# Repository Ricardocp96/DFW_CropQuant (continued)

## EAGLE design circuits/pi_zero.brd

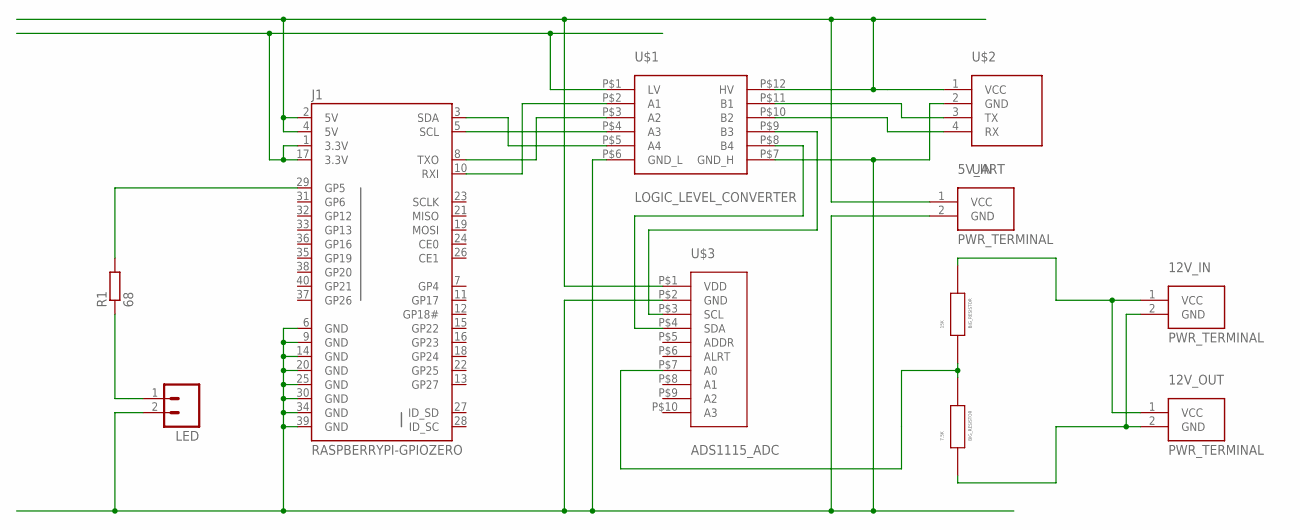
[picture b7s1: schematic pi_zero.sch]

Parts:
5V_IN, 12V_IN, 12V_OUT: PWR_TERMINAL
7.5K, 15K: BIG_RESISTOR
J1: RASPBERRYPI-GPIOZERO; 2X20-ZERO
LED: M02LOCK_LONGPADS; 1X02_LOCK_LONGPADS
R1: 68; 0204/7
U$1: LOGIC_LEVEL_CONVERTER
U$2: UART; I2C_TERM
U$3: ADS1115_ADC

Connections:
unnamed: J1.29 (GP5), R1.2
unnamed: LED.1, R1.1
unnamed: U$1.P$11 (B1), U$2.3 (TX)
unnamed: 5V_IN.1 (VCC), J1.2 (5V), J1.4 (5V), U$1.P$12 (HV), U$2.1 (VCC), U$3.P$1 (VDD)
unnamed: J1.1 (3.3V), J1.17 (3.3V), U$1.P$1 (LV)
unnamed: 5V_IN.2 (GND), J1.6 (GND), J1.9 (GND), J1.14 (GND), J1.20 (GND), J1.25 (GND), J1.30 (GND), J1.34 (GND), J1.39 (GND), LED.2, U$1.P$6 (GND_L), U$1.P$7 (GND_H), U$2.2 (GND), U$3.P$2 (GND)
unnamed: 7.5K.P$1, 12V_IN.2 (GND), 12V_OUT.2 (GND)
unnamed: U$1.P$10 (B2), U$2.4 (RX)
unnamed: J1.10 (RXI), U$1.P$2 (A1)
unnamed: J1.8 (TXO), U$1.P$3 (A2)
unnamed: 7.5K.P$2, 15K.P$1, U$3.P$7 (A0)
unnamed: U$1.P$9 (B3), U$3.P$3 (SCL)
unnamed: 12V_IN.1 (VCC), 12V_OUT.1 (VCC), 15K.P$2
unnamed: U$1.P$8 (B4), U$3.P$4 (SDA)
unnamed: J1.3 (SDA), U$1.P$5 (A4)
unnamed: J1.5 (SCL), U$1.P$4 (A3)

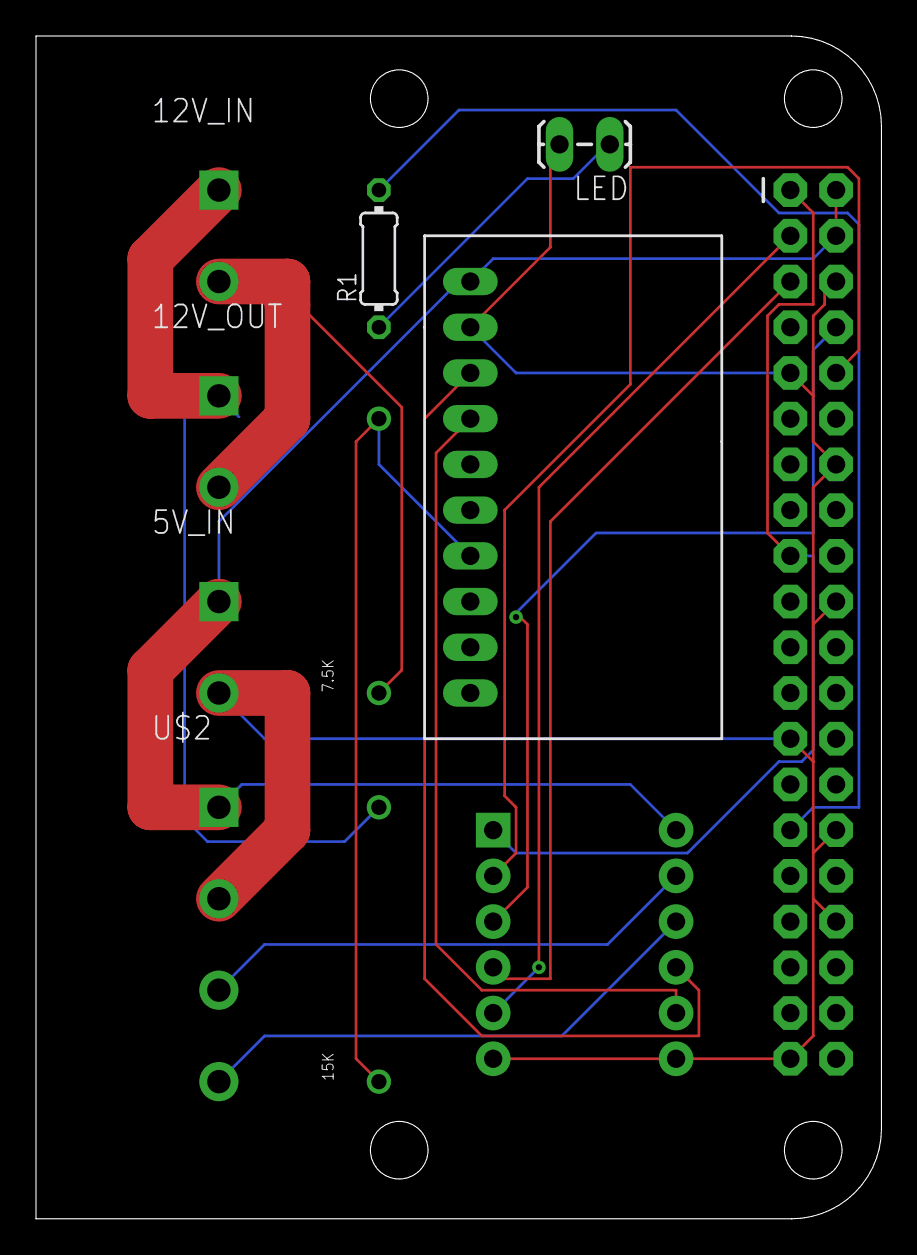
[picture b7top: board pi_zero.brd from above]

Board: 2 copper layers, 47.0 x 65.7 mm, 11 parts (0 on the bottom side), 16 nets.

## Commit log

2019-04-02 updated circuit schematics
2019-04-02 circuit update
2019-04-24 included source
